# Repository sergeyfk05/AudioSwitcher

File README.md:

# AudioSwitcher
Switch audio signals in priority
The new version of project by <a href="https://github.com/sergeyfk05/AudioSwitcherSTM">link</a>.

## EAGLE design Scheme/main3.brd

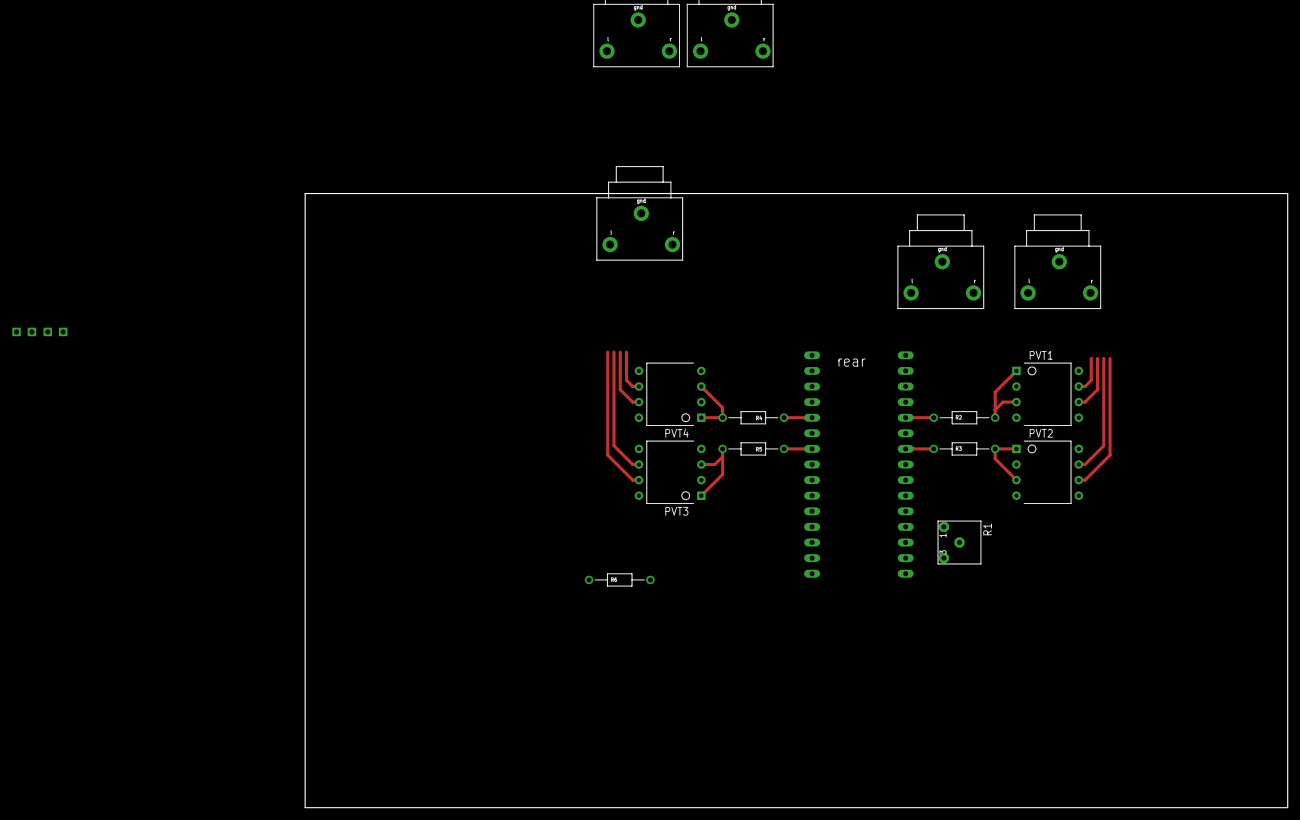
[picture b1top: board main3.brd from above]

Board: 2 copper layers, 160.0 x 100.0 mm, 18 parts (0 on the bottom side), 25 nets.

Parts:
MJ1, MJ2, MJ3, MJ4, MJ5: MINIJACKF
PVT1, PVT2, PVT3, PVT4: PVT322A; DIP-8
R1: 3362H
R2, R3, R4, R5, R6: CF-25(C1-4)
U$1: NANO
U$2, U$3: 2PINCONNECTOR; 2PIN

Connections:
unnamed: R1.3, U$1.3.3V
unnamed: R1.2, U$1.AREF
unnamed: R1.1, U$1.A0
unnamed: MJ1.LEFT, PVT2.6, U$1.A4
unnamed: PVT2.1, PVT2.3, R3.P$2
unnamed: PVT1.1, PVT1.3, R2.P$2
unnamed: R2.P$1, U$1.A7
unnamed: R3.P$1, U$1.A5
unnamed: R5.P$1, U$1.D4
unnamed: R4.P$1, U$1.D2
unnamed: MJ1.RIGHT, PVT2.7
unnamed: PVT3.1, PVT3.3, R5.P$2
unnamed: PVT4.1, PVT4.3, R4.P$2
unnamed: U$1.D8, U$2.P$1
unnamed: MJ2.LEFT, PVT1.6, U$1.A6
unnamed: MJ2.RIGHT, PVT1.7
unnamed: R6.P$2, U$1.D9
unnamed: MJ5.RIGHT, PVT1.8, PVT2.8
unnamed: MJ4.LEFT, PVT4.6
unnamed: MJ4.RIGHT, PVT4.7, U$1.D3
unnamed: MJ3.LEFT, PVT3.6
unnamed: MJ3.RIGHT, PVT3.7, U$1.D5
unnamed: R6.P$1, U$3.P$1
unnamed: MJ5.LEFT, PVT1.5, PVT2.5, PVT3.5, PVT3.8, PVT4.5, PVT4.8
unnamed: MJ1.GND, MJ2.GND, MJ3.GND, MJ4.GND, MJ5.GND, PVT1.2, PVT1.4, PVT2.2, PVT2.4, PVT3.2, PVT3.4, PVT4.2, PVT4.4, U$1.GND1, U$2.P$2, U$3.P$2

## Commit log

2019-04-27 init
2019-05-11 3d models and more quality program
